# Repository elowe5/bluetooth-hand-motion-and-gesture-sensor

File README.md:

# bluetooth-hand-motion-and-gesture-sensor
Hackaday.io Flexible pcb contest entry

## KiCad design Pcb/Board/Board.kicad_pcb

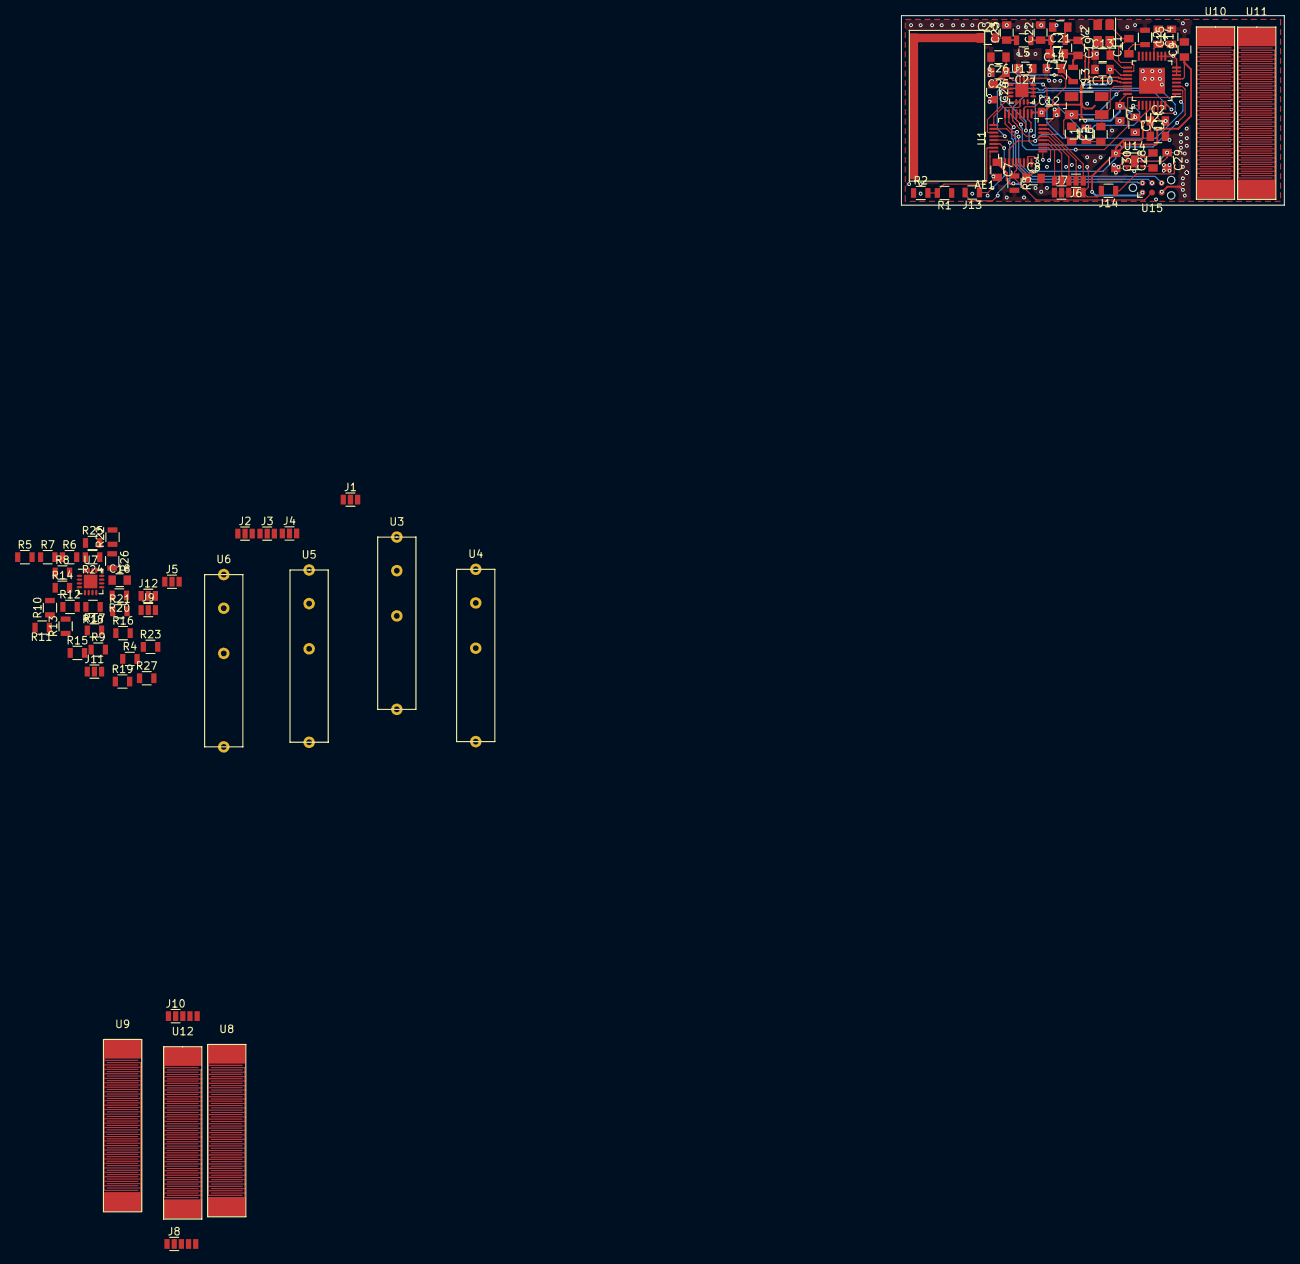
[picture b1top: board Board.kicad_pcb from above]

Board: 2 copper layers, 50.8 x 25.1 mm, 94 parts (0 on the bottom side), 84 nets.

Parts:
AE1: Antenna; antenna
C1, C2, C3, C4, C5, C6, C7, C8, C9, C10, C11, C12, C13, C14, C15, C16, C17, C19, C20, C21, C22, C23, C28, C29, C30: C; C_0805
C18, C24: 10n; C_0805
C25, C27: 100n; C_0805
C26: 2u2; C_0805
J1, J2, J3, J4: Conn_01x03_Male; conn3
J5, J9, J11, J12: Conn_01x03_Female; conn3
J6, J7: Conn_01x05_Female; conn5
J8, J10: Conn_01x05_Male; conn5
J13: Conn_01x02_Female; R_0805
J14: Conn_01x02_Male; R_0805
L1, L2, L3, L4, L5: INDUCTOR; R_0805
R1, R2, R3: Short; R_0805
R4, R5, R10, R11, R16, R17, R22, R23: R; R_0805
R6, R7, R8, R9, R12, R13, R14, R15, R18, R19, R20, R21, R24, R25, R26, R27: Rshort; R_0805
U1: STM32F302x6; LQFP-32_5x5mm_Pitch0.5mm
U2: BLUENRG-MS; LQFP-32-1EP_5x5mm_Pitch0.5mm
U3, U4, U5, U6: RSTRAIN; Rstrain
U7: TSV524; QFN-16-1EP_3x3mm_Pitch0.5mm
U8, U9, U10, U11, U12: CSTRAIN; Cstrain
U13: ICM-20602; UQFN-16-1EP_3x3mm_Pitch0.5mm
U14: REG71050 3.3V; DFN-6-1EP_2x2mm_Pitch0.65mm
U15: TagConnect; Tag-Connect_TC2030-IDC-NL
Y1: Crystal; Crystal_SMD_Abracon_ABM3B-4pin_5.0x3.2mm
Y2: Crystal; Crystal_SMD_SeikoEpson_TSX3225-4pin_3.2x2.5mm

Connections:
+3V3: C1.1, C4.1, C7.1, C8.1, C9.1, C10.1, C12.1, C18.1, C24.1, C25.1, C26.1, C30.1, R1.1, U1.1, U1.5, U1.17, U2.5, U2.19, U2.24, U2.27, U2.28, U7.11, U13.1, U13.16, U14.1, U15.1
+BATT: C29.1, J14.1, U14.3, U14.5
/accint: U1.25, U13.6
/async: U1.22, U13.8
/btint: U1.18, U2.3
/btnrst: U1.19, U2.25
/csacc: U1.27, U13.5
/csbt: U1.28, U2.31
/miso: U1.20, U2.32, U13.4
/mosi: U1.21, U2.1, U13.3
/nrst: R3.1, U1.4, U15.3
/rf+: C17.1, C19.2, L3.1, U2.21
/rf-: C19.1, C21.1, L4.1, U2.20
/spiclk: U1.2, U2.2, U13.2
/swclk: U1.24, U15.4
/swdio: U1.23, U15.2
/swo: U1.26, U15.6
/uartRX: J13.1, U1.30
/uartTX: J13.2, U1.29
/vc: R4.1, R5.1, R10.1, R11.1, R16.1, R17.1, R22.1, R23.1, U1.3
/vout1: R6.2, U1.7, U7.15
/vout2: R12.2, U1.8, U7.6
/vout3: R18.2, U1.9, U7.7
/vout4: R24.2, U1.10, U7.14
/vstrain1: J6.5, U1.11
/vstrain2: J6.4, U1.12
/vstrain3: J6.3, U1.13
/vstrain4: J6.2, U1.14
/vstrain5: J6.1, U1.15
GND: C1.2, C2.2, C3.2, C4.2, C7.2, C8.2, C9.2, C10.2, C12.2, C13.1, C14.1, C15.2, C16.1, C18.2, C21.2, C22.2, C23.2, C24.2, C25.2, C26.2, C27.2, C29.2, C30.2, J5.2, J7.1, J7.2, J7.3, J7.4, J7.5, J9.2, J11.2, J12.2, J14.2, L1.2, L2.1, R2.1, R3.2, R9.2, R15.2, R21.2, R27.2, U1.6, U1.16, U1.32, U2.6, U2.7, U2.8, U2.9, U2.10, U2.11, U2.30, U2.33, U7.2, U13.9, U13.10, U13.11, U13.12, U13.13, U13.15, U14.2, U15.5
unnamed: AE1.1, C20.1
unnamed: C2.1, C3.1, U2.29
unnamed: C5.1, C6.1, L1.1
unnamed: C5.2, U2.23, Y1.1
unnamed: C6.2, U2.22, Y1.2
unnamed: C11.1, L2.2
unnamed: C11.2, U2.18, Y2.2
unnamed: C13.2, U2.17, Y2.1
unnamed: C14.2, C15.1, U2.12
unnamed: C16.2, L3.2
unnamed: C17.2, C22.1, L4.2, L5.1
unnamed: C20.2, C23.1, L5.2
unnamed: C27.1, U13.14
unnamed: C28.1, U14.4
unnamed: C28.2, U14.6
unnamed: J1.1, U3.3
unnamed: J1.2, U3.2, U3.4
unnamed: J1.3, U3.1
unnamed: J2.1, U4.3
unnamed: J2.2, U4.2, U4.4
unnamed: J2.3, U4.1
unnamed: J3.1, U5.3
unnamed: J3.2, U5.2, U5.4
unnamed: J3.3, U5.1
unnamed: J4.1, U6.3
unnamed: J4.2, U6.2, U6.4
unnamed: J4.3, U6.1
unnamed: J5.1, R4.2, R8.1
unnamed: J5.3, R5.2, R7.1
unnamed: J8.1, U12.1
unnamed: J8.2, U11.1
unnamed: J8.3, U10.1
unnamed: J8.4, U9.1
unnamed: J8.5, U8.1
unnamed: J9.1, R10.2, R14.1
unnamed: J9.3, R11.2, R13.1
unnamed: J10.1, U12.2
unnamed: J10.2, U11.2
unnamed: J10.3, U10.2
unnamed: J10.4, U9.2
unnamed: J10.5, U8.2
unnamed: J11.1, R16.2, R20.1
unnamed: J11.3, R17.2, R19.1
unnamed: J12.1, R22.2, R26.1
unnamed: J12.3, R23.2, R25.1
unnamed: R1.2, R2.2, U1.31
unnamed: R6.1, R7.2, U7.16
unnamed: R8.2, R9.1, U7.1
unnamed: R12.1, R13.2, U7.5
unnamed: R14.2, R15.1, U7.4
unnamed: R18.1, R19.2, U7.8
unnamed: R20.2, R21.1, U7.9
unnamed: R24.1, R25.2, U7.13
unnamed: R26.2, R27.1, U7.12

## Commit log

2019-05-19 added gerbers
